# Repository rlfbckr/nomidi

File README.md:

# NOMIDI
**A [OSC](http://opensoundcontrol.org/) based performance controller**

I build this controller out of frustration that [MIDI controllers](https://en.wikipedia.org/wiki/MIDI_controller) are still using only 7 bit resolution. **NOMIDI** is a OSC based controller with 10 channels each 10bit (12 or 14 bit should be possible as well) resolution for the sliders and knobs. The controller is based on a Teensy 4.1 microcontroller including a high speed ethernet port to broadcast and receive OSC to and from different nodes in the network.
 
**PLEAYSE NOTE:** NOMIDI is OSC based in cannot be used in an "MIDI Environment". I can send/reicive only signals form OSC enabled Software and Hardware. e.g. MaxMSP, Supercollider, PureData, Processing, OpenFrameworks, monome norns, Abelton Live and many more.

## Control elements
* inputs:
  - 10 x 2 knobs (potentiometer ALPS)
  - 10 x 2 pushbuttons
  - 10 x 1 slider (potentiometer 6mm ALPS)
* outputs: 
  - 10 x 1 seven-segment element (13,5mm)
  - 10 x 1 white led (3mm)

## Interface / Connection
- USB SlipSerial
**or**
- Ethernet

## PCB (Printed circuit board)

## Software
*For flashing the firmware on the Teensy board these software compnents are needed:*

- Arduino IDE (Version 1.8.13) [(download)](https://www.arduino.cc/en/software)
- Teensyduino (Version 1.53) [(download)](https://www.pjrc.com/teensy/td_download.html)

## Required Arduino libraries
- OSCBundle  *[install via package manager]*
- Chrono  *[install via package manager]*
- MUX74HC4067 *[install via package manager]*
- SevSeg ( Seven Segment Multiplexing Library ) *[modefied version included in firmware sketch]*
- NativeEthernet ( Teensy 4.1 ) *[comes with teensyduino]*

## Bill of Materials
[BOM](https://docs.google.com/spreadsheets/d/1EoTag_wGxFKfiME3yydL2qvFMf1TQeLivOXvCBYUS_A/edit#gid=0)

## Firmware configuration

NOMIDI can communicate ether via *Ethernet* oder *Serial* (OSC over SLIPSerial). edit **firmware/nomidi_firmware/config.h**  

### Use Serial ( OSC over SLIP Serial) for communication:
```
#define USE_SLIP_SERIAL
```

### Use Ethernet ( OSC over UDP) for communication:
```
#define USE_ETHERNET

static byte mac[] = { 0xDE, 0xAD, 0xBE, 0xEF, 0xFC, 0x88}; // hardware addres of your device
static IPAddress myIP(10, 0, 0, 123); // ip address of the controller
static IPAddress serverIP(10, 0, 0, 3); // ip addres of your laptop
static int serverPort = 9013;
static int incommingPort = 10013;

```

## Teensy Settings
```
Borad:      Teensy 4.1
USB Type:   USB Serial
CPU Speed:  600 Mhz
```

## OSC messages

### NOMDI -> software

Potentiometer 1 (top row)
```
/nm/p0 [0-4095] [0-4095] [0-4095] [0-4095] [0-4095] [0-4095] [0-4095] [0-4095] [0-4095] [0-4095]
```
Potentiometer 0 (bottom row)
```
/nm/p1 [0-4095] [0-4095] [0-4095] [0-4095] [0-4095] [0-4095] [0-4095] [0-4095] [0-4095] [0-4095]
```
Button 1 (top row)
```
/nm/p1 [0/1] [0/1] [0/1] [0/1] [0/1] [0/1] [0/1] [0/1] [0/1] [0/1]
```
Fader
```
/nm/f [0-4095] [0-4095] [0-4095] [0-4095] [0-4095] [0-4095] [0-4095] [0-4095] [0-4095] [0-4095]
```
Button 0 (bottom row)
```
/nm/p0 [0/1] [0/1] [0/1] [0/1] [0/1] [0/1] [0/1] [0/1] [0/1] [0/1]
```

### software -> NOMIDI
LED (single)
```
/nm/setled <pos 0-9> <brightness 0-100>
```
7Segment (single segment)
```
/nm/set7set <pos 0-9> <character>
```

7Segment (all segments)
```
/nm/set7segall <character> <character> <character> <character> <character> <character> <character> <character> <character> <character>
```

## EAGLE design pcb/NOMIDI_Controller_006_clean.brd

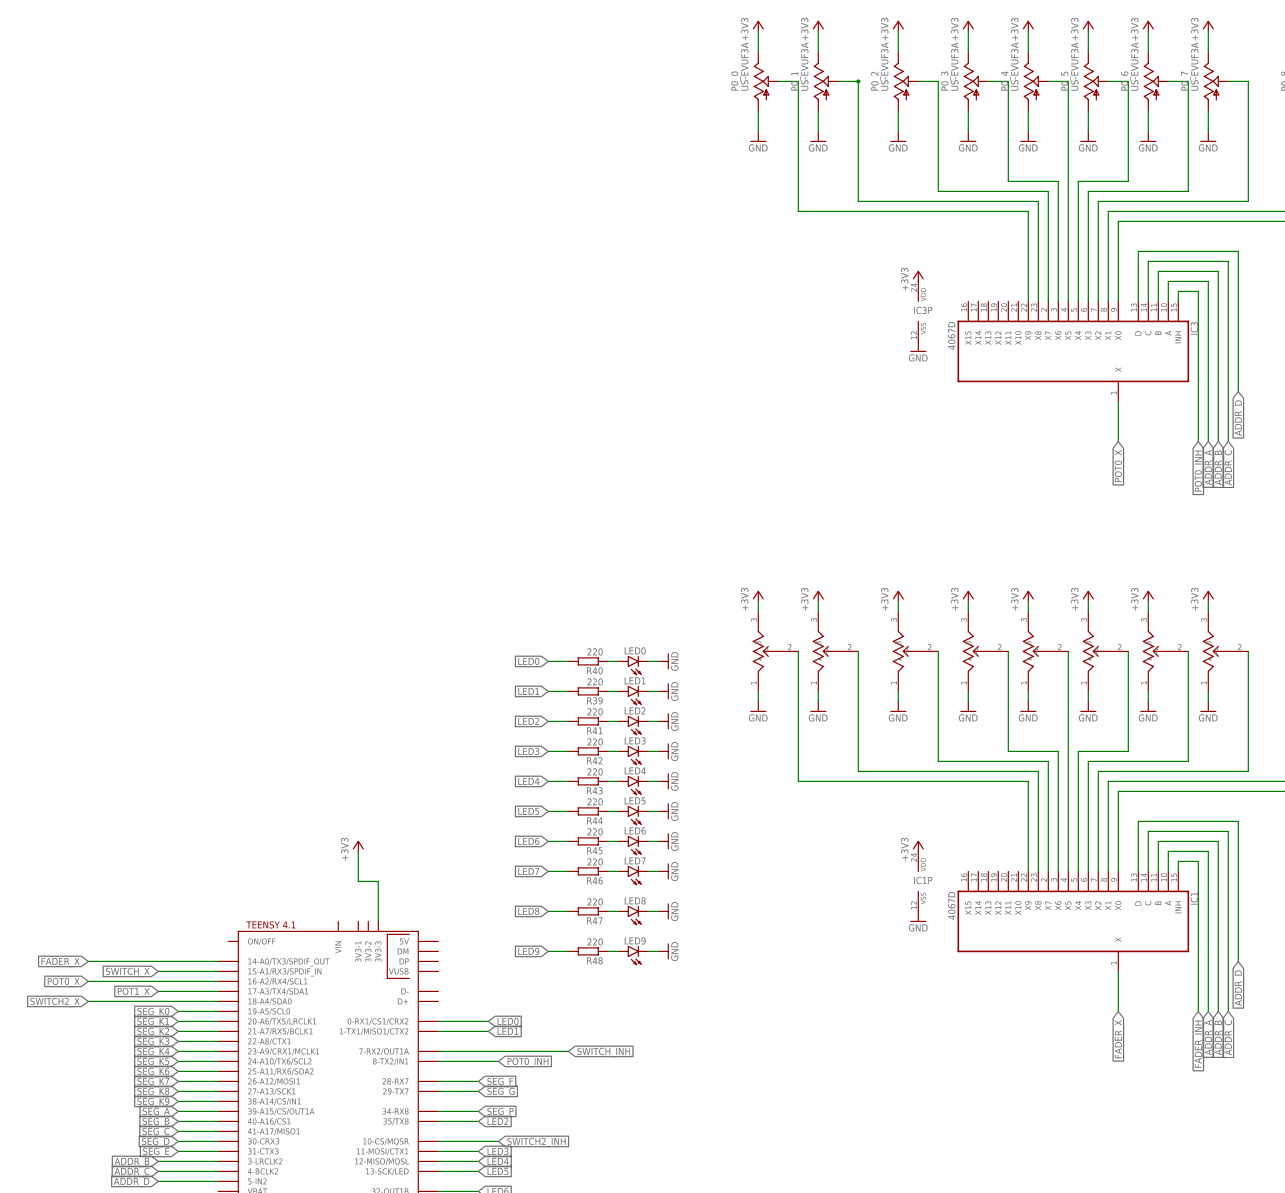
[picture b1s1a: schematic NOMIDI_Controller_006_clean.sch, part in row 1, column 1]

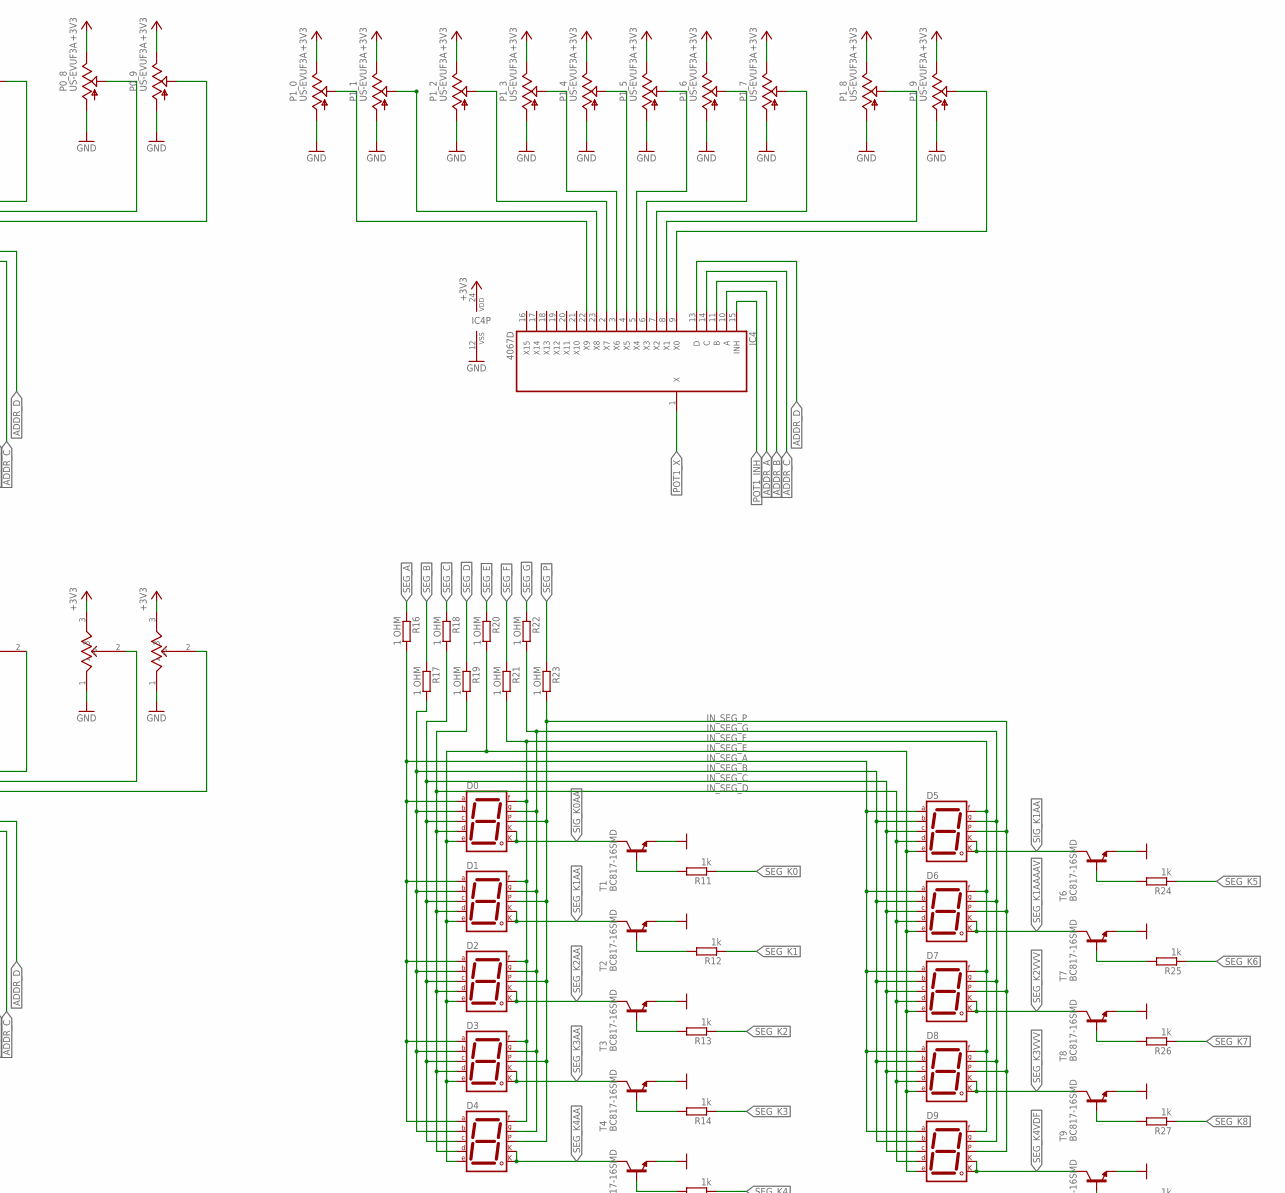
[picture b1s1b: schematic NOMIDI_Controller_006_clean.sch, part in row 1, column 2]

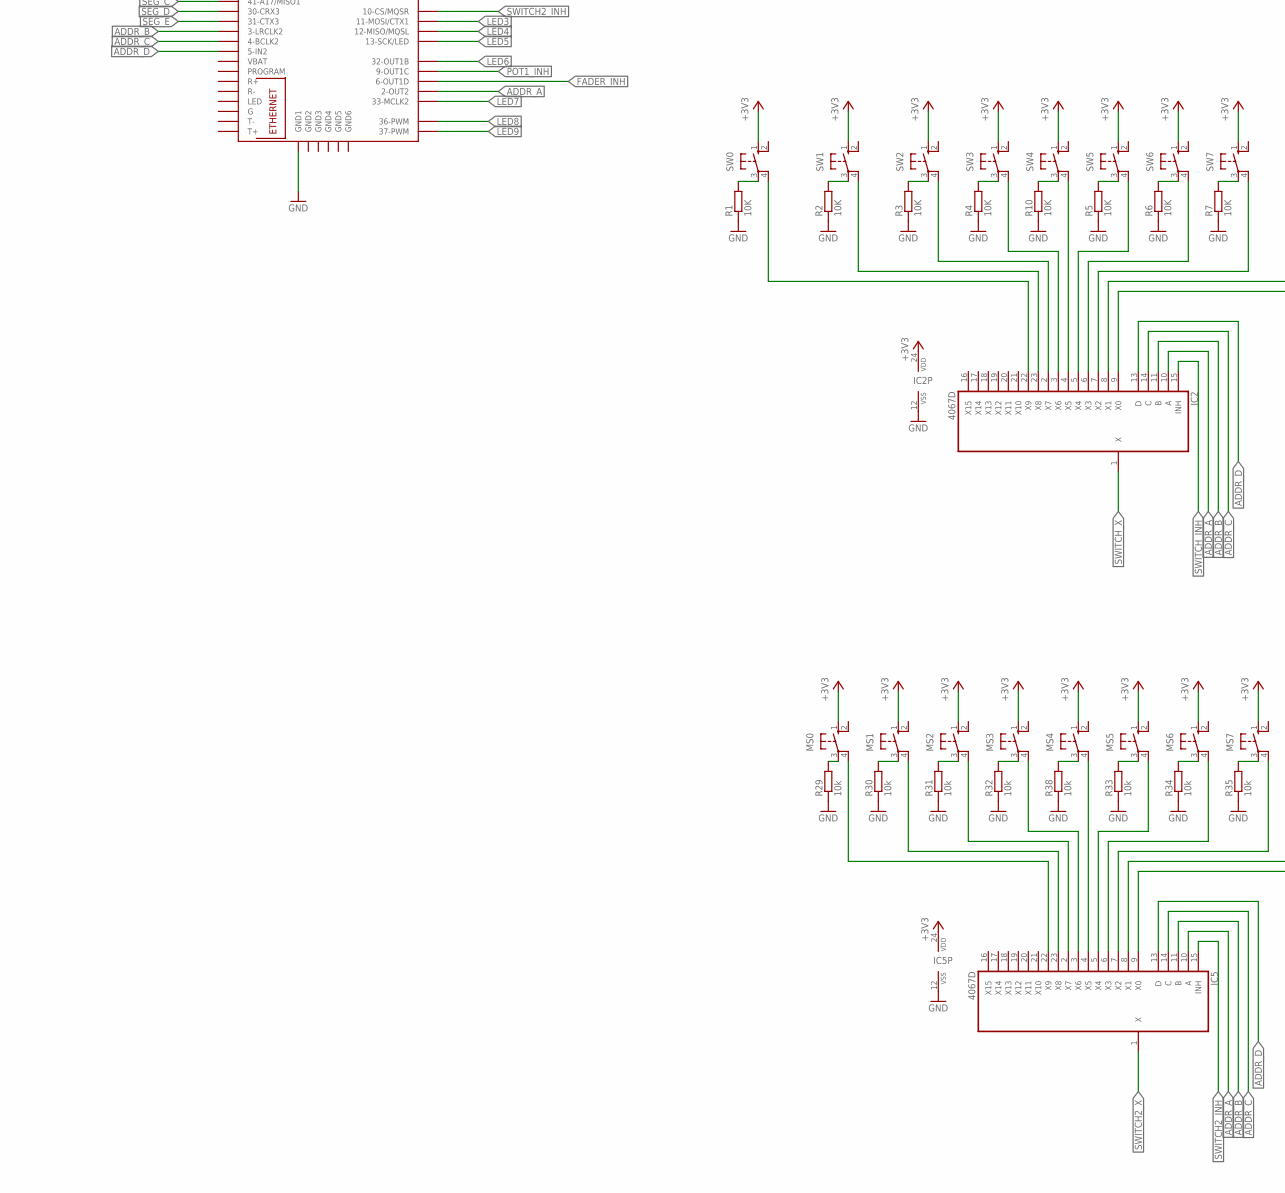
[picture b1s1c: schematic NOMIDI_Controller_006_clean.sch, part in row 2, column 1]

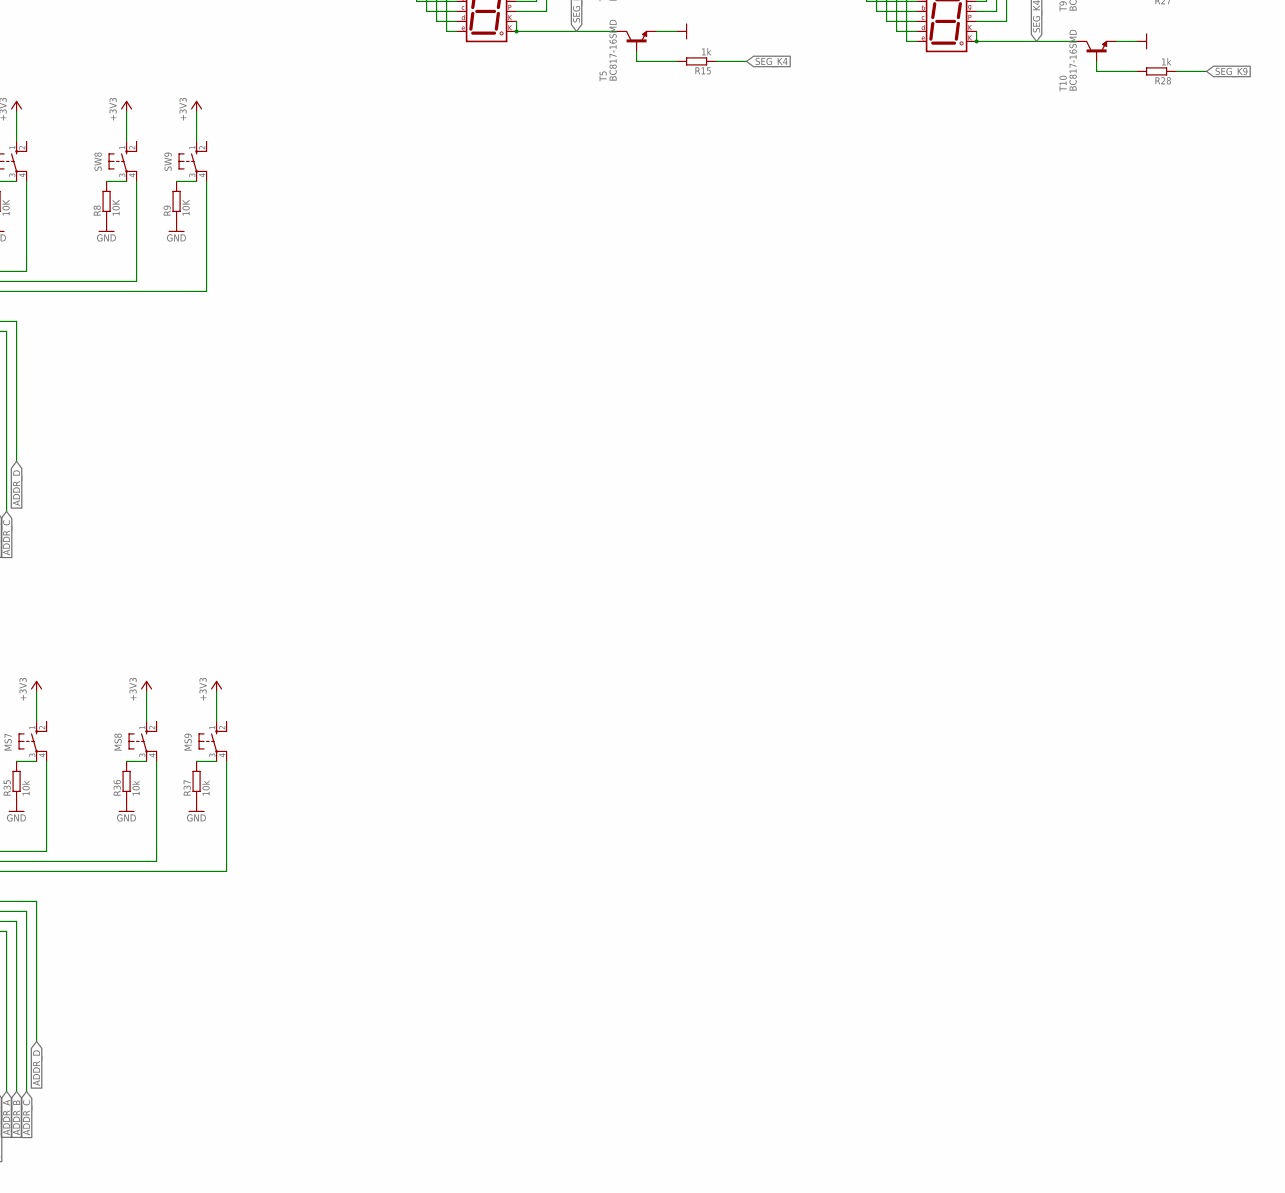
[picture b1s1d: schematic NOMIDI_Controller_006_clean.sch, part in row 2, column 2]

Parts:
D0, D1, D2, D3, D4, D5, D6, D7, D8, D9: 7SEG-CK; 7SEG-13
IC1, IC2, IC3, IC4, IC5: 4067D; SO24W
LED0, LED1, LED2, LED3, LED4, LED5, LED6, LED7, LED8, LED9: LED3MM
M0, M1: SLIDEPOT-ALPS-60MM; RS6011SP600
MS0, MS1, MS2, MS3, MS4, MS5, MS6, MS7, MS8, MS9: 10-XX; B3F-10XX
P0_0, P0_1, P0_2, P0_3, P0_4, P0_5, P0_6, P0_7, P0_8, P0_9, P1_0, P1_1, P1_2, P1_3, P1_4, P1_5, P1_6, P1_7, P1_8, P1_9: US-EVUF3A; EVUF
R1, R2, R3, R4, R5, R6, R7, R8, R9, R10: 10K; 0207/7
R11, R12, R13, R14, R15, R24, R25, R26, R27, R28: 1k; 0207/7
R16, R17, R18, R19, R20, R21, R22, R23: 1 OHM; 0207/7
R29, R30, R31, R32, R33, R34, R35, R36, R37, R38: 10k; 0207/7
R39, R40, R41, R42, R43, R44, R45, R46, R47, R48: 220; 0207/7
S0, S1, S2, S3, S4, S5, S6, S7: SLIDEPOT-ALPS-60MM; RS6011SP600
SW0, SW1, SW2, SW3, SW4, SW5, SW6, SW7, SW8, SW9: 10-XX; B3F-10XX
T1, T2, T3, T4, T5, T6, T7, T8, T9, T10: BC817-16SMD; SOT23-BEC
U$1: TEENSY41

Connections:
+3V3: IC1.24 (VDD), IC2.24 (VDD), IC3.24 (VDD), IC4.24 (VDD), IC5.24 (VDD), M0.3, M1.3, MS0.1 (S), MS1.1 (S), MS2.1 (S), MS3.1 (S), MS4.1 (S), MS5.1 (S), MS6.1 (S), MS7.1 (S), MS8.1 (S), MS9.1 (S), P0_0.3 (E), P0_1.3 (E), P0_2.3 (E), P0_3.3 (E), P0_4.3 (E), P0_5.3 (E), P0_6.3 (E), P0_7.3 (E), P0_8.3 (E), P0_9.3 (E), P1_0.3 (E), P1_1.3 (E), P1_2.3 (E), P1_3.3 (E), P1_4.3 (E), P1_5.3 (E), P1_6.3 (E), P1_7.3 (E), P1_8.3 (E), P1_9.3 (E), S0.3, S1.3, S2.3, S3.3, S4.3, S5.3, S6.3, S7.3, SW0.1 (S), SW1.1 (S), SW2.1 (S), SW3.1 (S), SW4.1 (S), SW5.1 (S), SW6.1 (S), SW7.1 (S), SW8.1 (S), SW9.1 (S), U$1.3V3-3
ADDR_A: IC1.10 (A), IC2.10 (A), IC3.10 (A), IC4.10 (A), IC5.10 (A), U$1.2-OUT2
ADDR_B: IC1.11 (B), IC2.11 (B), IC3.11 (B), IC4.11 (B), IC5.11 (B), U$1.3-LRCLK2
ADDR_C: IC1.14 (C), IC2.14 (C), IC3.14 (C), IC4.14 (C), IC5.14 (C), U$1.4-BCLK2
ADDR_D: IC1.13 (D), IC2.13 (D), IC3.13 (D), IC4.13 (D), IC5.13 (D), U$1.5-IN2
FADER_INH: IC1.15 (INH), U$1.6-OUT1D
FADER_X: IC1.1 (X), U$1.14-A0/TX3/SPDIF_OUT
GND: IC1.12 (VSS), IC2.12 (VSS), IC3.12 (VSS), IC4.12 (VSS), IC5.12 (VSS), LED0.K (C), LED1.K (C), LED2.K (C), LED3.K (C), LED4.K (C), LED5.K (C), LED6.K (C), LED7.K (C), LED8.K (C), LED9.K (C), M0.1, M1.1, P0_0.1 (A), P0_1.1 (A), P0_2.1 (A), P0_3.1 (A), P0_4.1 (A), P0_5.1 (A), P0_6.1 (A), P0_7.1 (A), P0_8.1 (A), P0_9.1 (A), P1_0.1 (A), P1_1.1 (A), P1_2.1 (A), P1_3.1 (A), P1_4.1 (A), P1_5.1 (A), P1_6.1 (A), P1_7.1 (A), P1_8.1 (A), P1_9.1 (A), R1.1, R2.1, R3.1, R4.1, R5.1, R6.1, R7.1, R8.1, R9.1, R10.1, R29.1, R30.1, R31.1, R32.1, R33.1, R34.1, R35.1, R36.1, R37.1, R38.1, S0.1, S1.1, S2.1, S3.1, S4.1, S5.1, S6.1, S7.1, T1.E, T2.E, T3.E, T4.E, T5.E, T6.E, T7.E, T8.E, T9.E, T10.E, U$1.GND1
IN_SEG_A: D0.7 (A), D1.7 (A), D2.7 (A), D3.7 (A), D4.7 (A), D5.7 (A), D6.7 (A), D7.7 (A), D8.7 (A), D9.7 (A), R16.2
IN_SEG_B: D0.6 (B), D1.6 (B), D2.6 (B), D3.6 (B), D4.6 (B), D5.6 (B), D6.6 (B), D7.6 (B), D8.6 (B), D9.6 (B), R17.2
IN_SEG_C: D0.4 (C), D1.4 (C), D2.4 (C), D3.4 (C), D4.4 (C), D5.4 (C), D6.4 (C), D7.4 (C), D8.4 (C), D9.4 (C), R18.2
IN_SEG_D: D0.2 (D), D1.2 (D), D2.2 (D), D3.2 (D), D4.2 (D), D5.2 (D), D6.2 (D), D7.2 (D), D8.2 (D), D9.2 (D), R19.2
IN_SEG_E: D0.1 (E), D1.1 (E), D2.1 (E), D3.1 (E), D4.1 (E), D5.1 (E), D6.1 (E), D7.1 (E), D8.1 (E), D9.1 (E), R20.2
IN_SEG_F: D0.9 (F), D1.9 (F), D2.9 (F), D3.9 (F), D4.9 (F), D5.9 (F), D6.9 (F), D7.9 (F), D8.9 (F), D9.9 (F), R21.2
IN_SEG_G: D0.10 (G), D1.10 (G), D2.10 (G), D3.10 (G), D4.10 (G), D5.10 (G), D6.10 (G), D7.10 (G), D8.10 (G), D9.10 (G), R22.2
IN_SEG_P: D0.5 (DP), D1.5 (DP), D2.5 (DP), D3.5 (DP), D4.5 (DP), D5.5 (DP), D6.5 (DP), D7.5 (DP), D8.5 (DP), D9.5 (DP), R23.2
LED0: R40.2, U$1.0-RX1/CS1/CRX2
LED1: R39.2, U$1.1-TX1/MISO1/CTX2
LED2: R41.2, U$1.35-TX8 (35/TX8)
LED3: R42.2, U$1.11-MOSI/CTX1
LED4: R43.2, U$1.12-MISO/MQSL
LED5: R44.2, U$1.13-SCK/LED
LED6: R45.2, U$1.32-OUT1B
LED7: R46.2, U$1.33-MCLK2
LED8: R47.2, U$1.36-PWM
LED9: R48.2, U$1.37-PWM
unnamed: IC1.22 (X9), S0.2
unnamed: IC1.9 (X0), M1.2
unnamed: IC1.8 (X1), M0.2
unnamed: IC2.9 (X0), SW9.4 (P1)
unnamed: IC1.7 (X2), S7.2
unnamed: IC1.6 (X3), S6.2
unnamed: IC1.5 (X4), S5.2
unnamed: IC1.4 (X5), S4.2
unnamed: IC1.3 (X6), S3.2
unnamed: IC1.2 (X7), S2.2
unnamed: IC1.23 (X8), S1.2
unnamed: IC2.8 (X1), SW8.4 (P1)
unnamed: IC2.7 (X2), SW7.4 (P1)
unnamed: IC2.6 (X3), SW6.4 (P1)
unnamed: IC2.5 (X4), SW5.4 (P1)
unnamed: IC3.9 (X0), P0_9.2 (S)
unnamed: IC2.3 (X6), SW3.4 (P1)
unnamed: IC2.2 (X7), SW2.4 (P1)
unnamed: IC2.23 (X8), SW1.4 (P1)
unnamed: IC2.22 (X9), SW0.4 (P1)
unnamed: R1.2, SW0.3
unnamed: R2.2, SW1.3
unnamed: IC3.8 (X1), P0_8.2 (S)
unnamed: R3.2, SW2.3
unnamed: IC3.7 (X2), P0_7.2 (S)
unnamed: R4.2, SW3.3
unnamed: IC3.6 (X3), P0_6.2 (S)
unnamed: R5.2, SW5.3
unnamed: IC3.5 (X4), P0_5.2 (S)
unnamed: R6.2, SW6.3
unnamed: IC3.4 (X5), P0_4.2 (S)
unnamed: R7.2, SW7.3
unnamed: IC3.3 (X6), P0_3.2 (S)
unnamed: R8.2, SW8.3
unnamed: IC3.2 (X7), P0_2.2 (S)
unnamed: R9.2, SW9.3
unnamed: IC2.4 (X5), SW4.4 (P1)
unnamed: R10.2, SW4.3
unnamed: IC3.23 (X8), P0_1.2 (S)
unnamed: IC3.22 (X9), P0_0.2 (S)
unnamed: IC4.9 (X0), P1_9.2 (S)
unnamed: IC4.8 (X1), P1_8.2 (S)
unnamed: IC4.7 (X2), P1_7.2 (S)
unnamed: IC4.6 (X3), P1_6.2 (S)
unnamed: IC4.5 (X4), P1_5.2 (S)
unnamed: IC4.4 (X5), P1_4.2 (S)
unnamed: IC4.3 (X6), P1_3.2 (S)
unnamed: IC4.2 (X7), P1_2.2 (S)
unnamed: IC4.23 (X8), P1_1.2 (S)
unnamed: IC4.22 (X9), P1_0.2 (S)
unnamed: R11.2, T1.B
unnamed: R12.2, T2.B
unnamed: IC5.9 (X0), MS9.4 (P1)
unnamed: R13.2, T3.B
unnamed: R14.2, T4.B
unnamed: R15.2, T5.B
unnamed: IC5.8 (X1), MS8.4 (P1)
unnamed: IC5.7 (X2), MS7.4 (P1)
unnamed: IC5.6 (X3), MS6.4 (P1)
unnamed: IC5.5 (X4), MS5.4 (P1)
unnamed: IC5.3 (X6), MS3.4 (P1)
unnamed: IC5.2 (X7), MS2.4 (P1)
unnamed: IC5.23 (X8), MS1.4 (P1)
unnamed: R24.2, T6.B
unnamed: R25.2, T7.B
unnamed: R26.2, T8.B
unnamed: R27.2, T9.B
unnamed: R28.2, T10.B
unnamed: IC5.22 (X9), MS0.4 (P1)
unnamed: MS0.3, R29.2
unnamed: MS1.3, R30.2
unnamed: MS2.3, R31.2
unnamed: MS3.3, R32.2
unnamed: MS5.3, R33.2
unnamed: MS6.3, R34.2
unnamed: MS7.3, R35.2
unnamed: MS8.3, R36.2
unnamed: MS9.3, R37.2
unnamed: IC5.4 (X5), MS4.4 (P1)
unnamed: MS4.3, R38.2
unnamed: LED2.A, R41.1
unnamed: LED0.A, R40.1
unnamed: LED3.A, R42.1
unnamed: LED1.A, R39.1
unnamed: LED4.A, R43.1
unnamed: LED5.A, R44.1
unnamed: LED6.A, R45.1
unnamed: LED7.A, R46.1
unnamed: LED8.A, R47.1
unnamed: LED9.A, R48.1
POT0_INH: IC3.15 (INH), U$1.8-TX2/IN1
POT0_X: IC3.1 (X), U$1.16-A2/RX4/SCL1
POT1_INH: IC4.15 (INH), U$1.9-OUT1C
POT1_X: IC4.1 (X), U$1.17-A3/TX4/SDA1
SEG_A: R16.1, U$1.39-A15/CS/OUT1A
SEG_B: R17.1, U$1.40-A16/CS1
SEG_C: R18.1, U$1.41-A17/MISO1
SEG_D: R19.1, U$1.30-CRX3
SEG_E: R20.1, U$1.31-CTX3
SEG_F: R21.1, U$1.28-RX7
SEG_G: R22.1, U$1.29-TX7
SEG_K0: R11.1, U$1.19-A5/SCL0
SEG_K1: R12.1, U$1.20-A6/TX5/LRCLK1
SEG_K1AA: D1.3 (CK1), D1.8 (CK2), T2.C
SEG_K1AAAAV: D6.3 (CK1), D6.8 (CK2), T7.C
SEG_K2: R13.1, U$1.21-A7/RX5/BCLK1
SEG_K2AA: D2.3 (CK1), D2.8 (CK2), T3.C
SEG_K2VVV: D7.3 (CK1), D7.8 (CK2), T8.C
SEG_K3: R14.1, U$1.22-A8/CTX1
SEG_K3AA: D3.3 (CK1), D3.8 (CK2), T4.C
SEG_K3VVV: D8.3 (CK1), D8.8 (CK2), T9.C
SEG_K4: R15.1, U$1.23-A9/CRX1/MCLK1
SEG_K4AA: D4.3 (CK1), D4.8 (CK2), T5.C
SEG_K4VDF: D9.3 (CK1), D9.8 (CK2), T10.C
SEG_K5: R24.1, U$1.24-A10/TX6/SCL2
SEG_K6: R25.1, U$1.25-A11/RX6/SDA2
SEG_K7: R26.1, U$1.26-A12/MOSI1
SEG_K8: R27.1, U$1.27-A13/SCK1
SEG_K9: R28.1, U$1.38-A14/CS/IN1
SEG_P: R23.1, U$1.34-RX8
SIG_K0AA: D0.3 (CK1), D0.8 (CK2), T1.C
SIG_K1AA: D5.3 (CK1), D5.8 (CK2), T6.C
SWITCH2_INH: IC5.15 (INH), U$1.10-CS\MQSR (10-CS/MQSR)
SWITCH2_X: IC5.1 (X), U$1.18-A4/SDA0
SWITCH_INH: IC2.15 (INH), U$1.7-RX2/OUT1A
SWITCH_X: IC2.1 (X), U$1.15-A1/RX3/SPDIF_IN

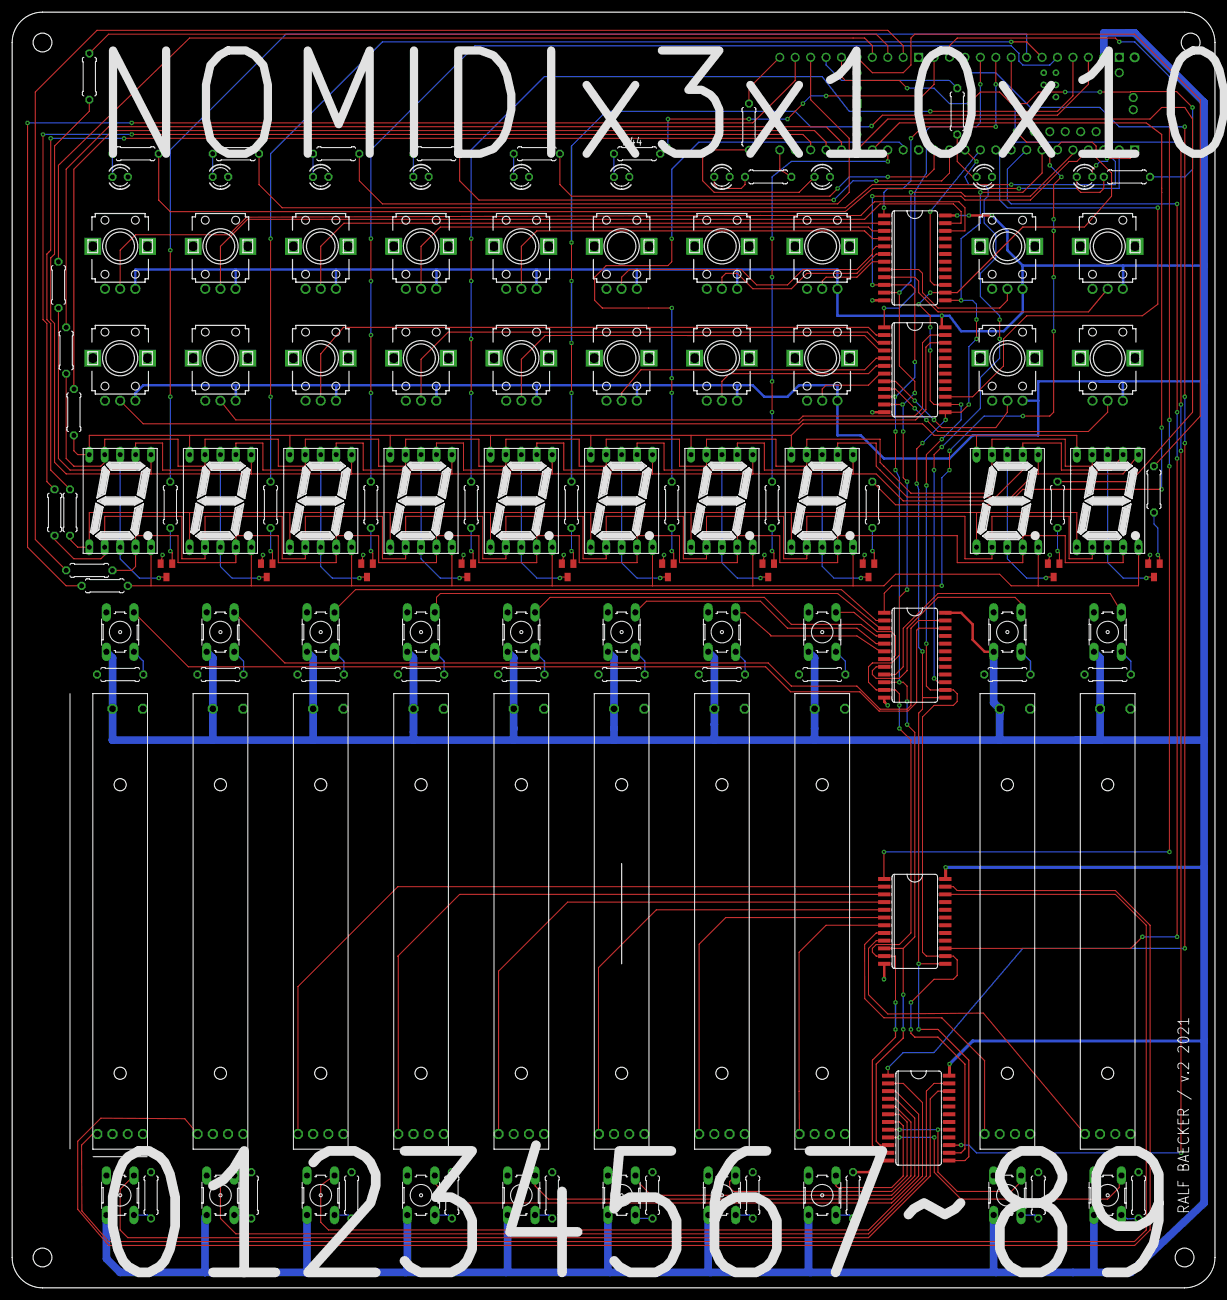
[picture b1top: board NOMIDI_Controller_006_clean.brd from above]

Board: 2 copper layers, 198.0 x 210.0 mm, 134 parts (1 on the bottom side), 152 nets.

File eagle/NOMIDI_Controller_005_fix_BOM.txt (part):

Partlist exported from C:/local/projekte/nomidi/eagle/NOMIDI_Controller_005_fix.sch at 2021-03-17 19:26

Part Value              Device             Package     Description                       MF MPN      OC_FARNELL OC_NEWARK POPULARITY SPICEPREFIX
D0                      7SEG-CK            7SEG-13     7-segment DISPLAY                                                  3                     
D1                      7SEG-CK            7SEG-13     7-segment DISPLAY                                                  3                     
D2                      7SEG-CK            7SEG-13     7-segment DISPLAY                                                  3                     
D3                      7SEG-CK            7SEG-13     7-segment DISPLAY                                                  3                     
D4                      7SEG-CK            7SEG-13     7-segment DISPLAY                                                  3                     
D5                      7SEG-CK            7SEG-13     7-segment DISPLAY                                                  3                     
D6                      7SEG-CK            7SEG-13     7-segment DISPLAY                                                  3                     
D7                      7SEG-CK            7SEG-13     7-segment DISPLAY                                                  3                     
D8                      7SEG-CK            7SEG-13     7-segment DISPLAY                                                  3                     
D9                      7SEG-CK            7SEG-13     7-segment DISPLAY                                                  3                     
IC1  4067D              4067D              SO24W       16-channel ANALOG MULTIPLEXER                                      0                     
IC2  4067D              4067D              SO24W       16-channel ANALOG MULTIPLEXER                                      0                     
IC3  4067D              4067D              SO24W       16-channel ANALOG MULTIPLEXER                                      0                     
IC4  4067D              4067D              SO24W       16-channel ANALOG MULTIPLEXER                                      0                     
IC5  4067D              4067D              SO24W       16-channel ANALOG MULTIPLEXER                                      0                     
LED0                    LED3MM             LED3MM      LED                                                                97                    
LED1                    LED3MM             LED3MM      LED                                                                97                    
LED2                    LED3MM             LED3MM      LED                                                                97                    
LED3                    LED3MM             LED3MM      LED                                                                97                    
LED4                    LED3MM             LED3MM      LED                                                                97                    
LED5                    LED3MM             LED3MM      LED                                                                97                    
LED6                    LED3MM             LED3MM      LED                                                                97                    
LED7                    LED3MM             LED3MM      LED                                                                97                    
LED8                    LED3MM             LED3MM      LED                                                                97                    
LED9                    LED3MM             LED3MM      LED                                                                97                    
M0   SLIDEPOT-ALPS-60MM SLIDEPOT-ALPS-60MM RS6011SP600                                                                                          
M1   SLIDEPOT-ALPS-60MM SLIDEPOT-ALPS-60MM RS6011SP600                                                                                          
MS0                     10-XX              B3F-10XX    OMRON SWITCH                         B3F-1000 176432     36M3542   72                    
MS1                     10-XX              B3F-10XX    OMRON SWITCH                         B3F-1000 176432     36M3542   72                    
MS2                     10-XX              B3F-10XX    OMRON SWITCH                         B3F-1000 176432     36M3542   72                    
MS3                     10-XX              B3F-10XX    OMRON SWITCH                         B3F-1000 176432     36M3542   72                    
MS4                     10-XX              B3F-10XX    OMRON SWITCH                         B3F-1000 176432     36M3542   72                    
MS5                     10-XX              B3F-10XX    OMRON SWITCH                         B3F-1000 176432     36M3542   72                    
MS6                     10-XX              B3F-10XX    OMRON SWITCH                         B3F-1000 176432     36M3542   72                    
MS7                     10-XX              B3F-10XX    OMRON SWITCH                         B3F-1000 176432     36M3542   72                    
MS8                     10-XX              B3F-10XX    OMRON SWITCH                         B3F-1000 176432     36M3542   72                    
MS9                     10-XX              B3F-10XX    OMRON SWITCH                         B3F-1000 176432     36M3542   72                    
P0_0 US-EVUF3A          US-EVUF3A          EVUF        9 mm Square Rotary Potentiometers                                  0                     
P0_1 US-EVUF3A          US-EVUF3A          EVUF        9 mm Square Rotary Potentiometers                                  0                     
P0_2 US-EVUF3A          US-EVUF3A          EVUF        9 mm Square Rotary Potentiometers                                  0                     
P0_3 US-EVUF3A          US-EVUF3A          EVUF        9 mm Square Rotary Potentiometers                                  0                     
P0_4 US-EVUF3A          US-EVUF3A          EVUF        9 mm Square Rotary Potentiometers                                  0                     
P0_5 US-EVUF3A          US-EVUF3A          EVUF        9 mm Square Rotary Potentiometers                                  0                     
P0_6 US-EVUF3A          US-EVUF3A          EVUF        9 mm Square Rotary Potentiometers                                  0                     
P0_7 US-EVUF3A          US-EVUF3A          EVUF        9 mm Square Rotary Potentiometers                                  0                     
P0_8 US-EVUF3A          US-EVUF3A          EVUF        9 mm Square Rotary Potentiometers                                  0                     
P0_9 US-EVUF3A          US-EVUF3A          EVUF        9 mm Square Rotary Potentiometers                                  0                     
P1_0 US-EVUF3A          US-EVUF3A          EVUF        9 mm Square Rotary Potentiometers                                  0                     
P1_1 US-EVUF3A          US-EVUF3A          EVUF        9 mm Square Rotary Potentiometers                                  0                     
P1_2 US-EVUF3A          US-EVUF3A          EVUF        9 mm Square Rotary Potentiometers                                  0                     
P1_3 US-EVUF3A          US-EVUF3A          EVUF        9 mm Square Rotary Potentiometers                                  0                     
P1_4 US-EVUF3A          US-EVUF3A          EVUF        9 mm Square Rotary Potentiometers                                  0                     
P1_5 US-EVUF3A          US-EVUF3A          EVUF        9 mm Square Rotary Potentiometers                                  0                     
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
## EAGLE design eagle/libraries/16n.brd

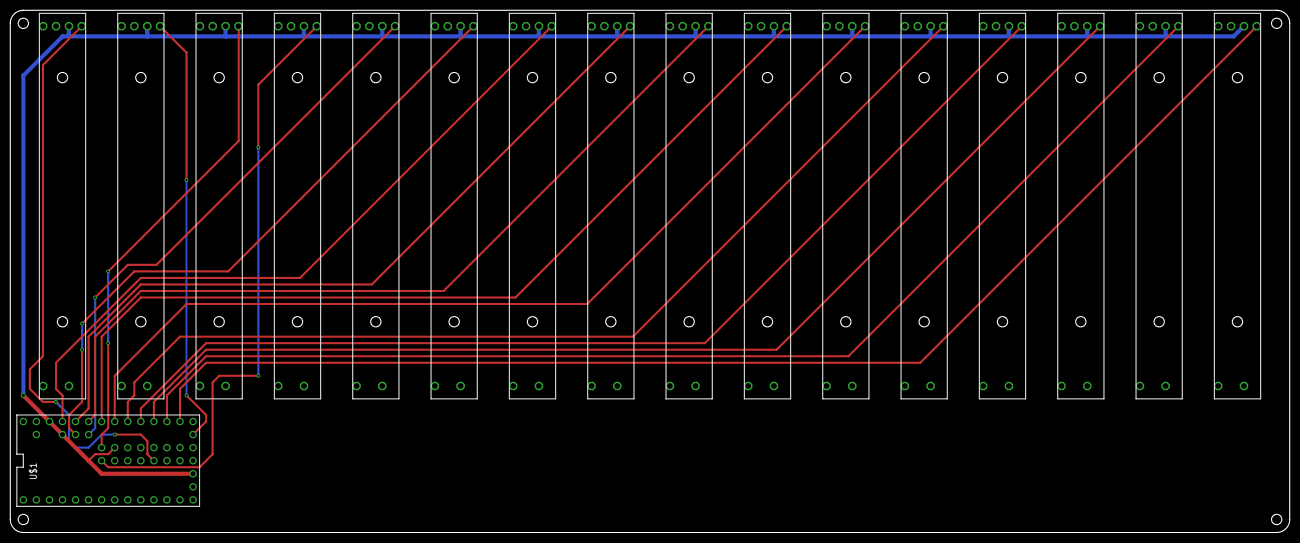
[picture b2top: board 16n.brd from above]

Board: 2 copper layers, 248.9 x 101.6 mm, 17 parts (0 on the bottom side), 18 nets.

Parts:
U$1: TEENSY_3.1_ALL_PINS_AND_PADS; TEENSY_3.1_ALLPINS
U$2, U$3, U$4, U$5, U$6, U$7, U$8, U$9, U$10, U$11, U$12, U$13, U$14, U$15, U$16, U$17: SLIDEPOT-ALPS-60MM; RS6011SP600

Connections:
+3V3: U$1.3.3V, U$1.3.3V1, U$1.3.3V2, U$1.AREF, U$2.1, U$3.1, U$4.1, U$5.1, U$6.1, U$7.1, U$8.1, U$9.1, U$10.1, U$11.1, U$12.1, U$13.1, U$14.1, U$15.1, U$16.1, U$17.1
A0: U$1.14/A0, U$2.2
A1: U$1.15/A1, U$3.2
A2: U$1.16/A2, U$4.2
A3: U$1.17/A3, U$5.2
A4: U$1.18/A4, U$6.2
A5: U$1.19/A5, U$7.2
A6: U$1.20/A6, U$8.2
A7: U$1.21/A7, U$9.2
A8: U$1.22/A8, U$10.2
A9: U$1.23/A9, U$11.2
A10: U$1.A10, U$12.2
A11: U$1.A11, U$13.2
A12: U$1.A12, U$14.2
A13: U$1.A13, U$15.2
A14: U$1.A14, U$16.2
A15: U$1.26, U$17.2
GND: U$1.AGND, U$1.GND, U$1.GND1, U$1.GND2, U$2.3, U$3.3, U$4.3, U$5.3, U$6.3, U$7.3, U$8.3, U$9.3, U$10.3, U$11.3, U$12.3, U$13.3, U$14.3, U$15.3, U$16.3, U$17.3

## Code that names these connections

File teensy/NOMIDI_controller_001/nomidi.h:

int segmentMax = 10;
volatile int lastSegmentPos = 0;

volatile int segmentPos = 0;
volatile int segmentTic = 0;
volatile char segmentData[] = "abcdefghij";
const int SEG_K[] = {19, 20, 21, 22, 23, 24, 25, 26, 27, 38};
const int SEG[] = {39, 40, 41, 30, 31, 28, 29, 34};
const int LED[] = {0, 1, 35, 11, 12, 13, 32, 33, 36, 37};
volatile int ledIntesity[] = { 0, 0, 0, 0, 0, 0, 0, 0, 0, 0};
volatile int softPWMtic = 0;
volatile int softPWMres = 100;
const int ADDR_A = 2;
const int ADDR_B = 3;
const int ADDR_C = 4;
const int ADDR_D = 5;

const int POT1_X = A3;
const int POT1_INH = 9;

const int POT0_X = A2;
const int POT0_INH = 8;

const int FADER_X = A0;
const int FADER_INH = 6;

const int SWITCH_X = 15;
const int SWITCH_INH = 7;


const int SWITCH2_X = A4;
const int SWITCH2_INH = 10;

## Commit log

2020-10-31 init..
2020-10-31 teensy
2020-10-31 cleanup
2020-10-31 naming...
2020-11-01 fixes..
2020-11-14 last
2021-01-29 pre STATE perfomance
2021-03-17 bom link
2021-03-18 images
2021-03-18 rename
2021-03-18 rename firemware
2021-03-19 use existing sevseg library
2021-03-19 update license
2021-03-19 7seg
2021-03-24 readme + slipserial
